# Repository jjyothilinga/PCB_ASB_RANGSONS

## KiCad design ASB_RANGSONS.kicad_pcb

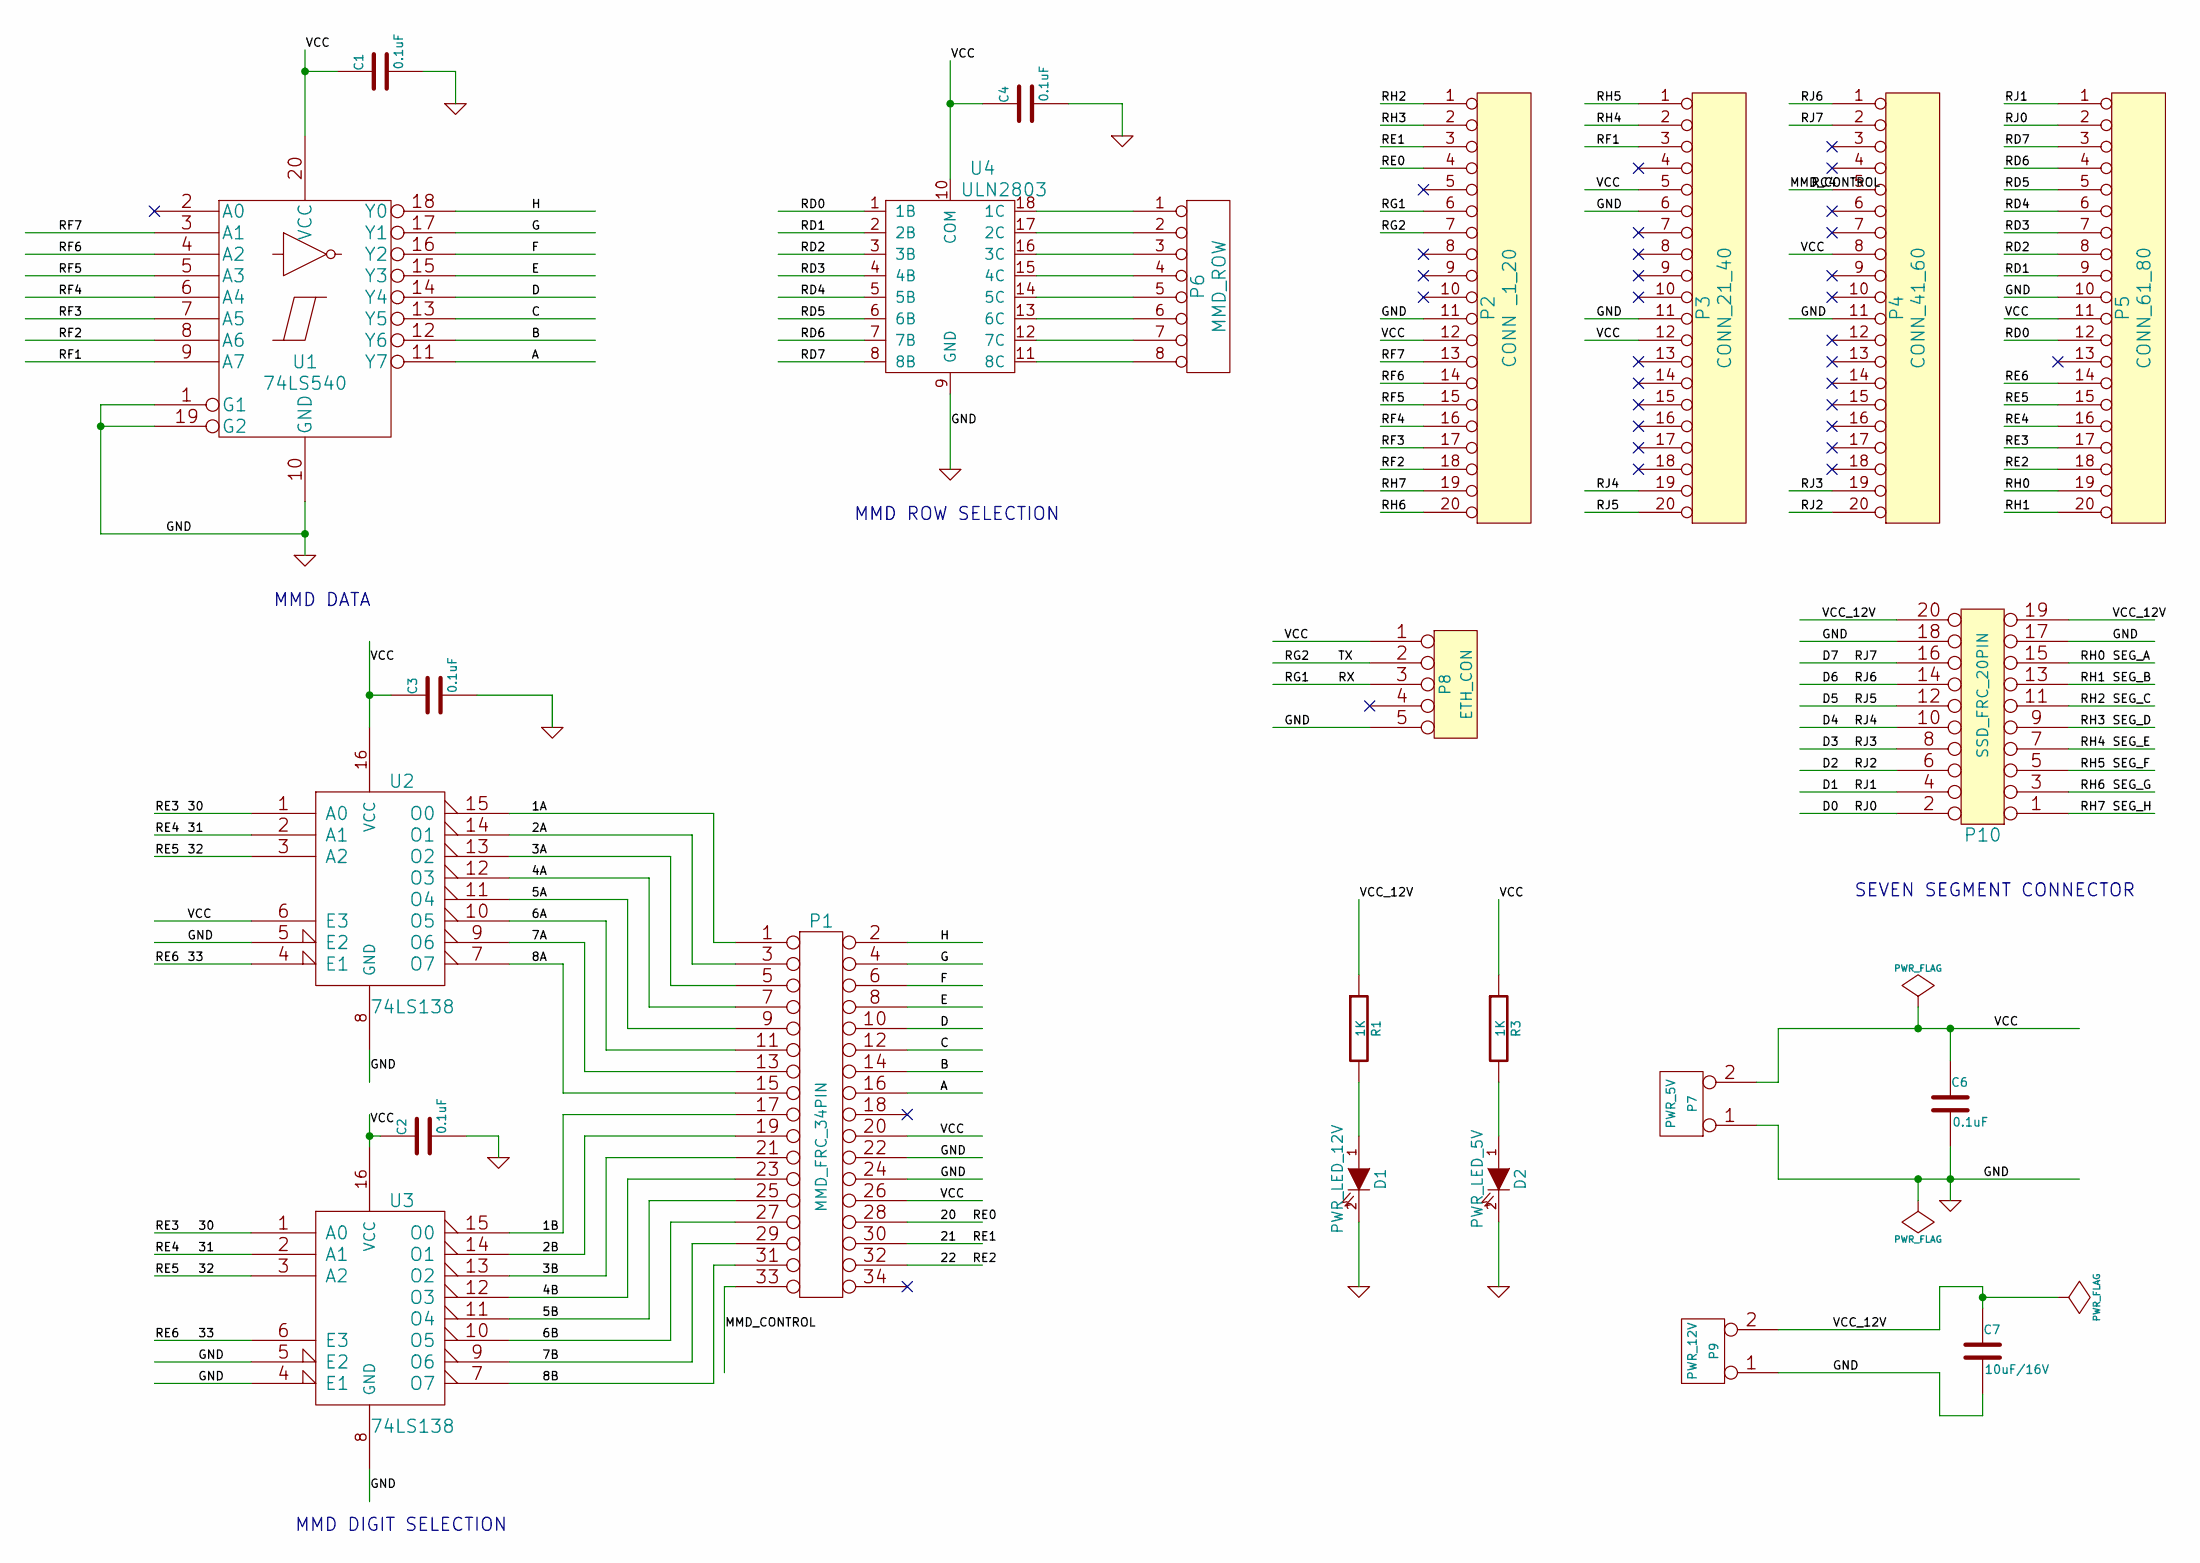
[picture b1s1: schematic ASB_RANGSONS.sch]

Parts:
C1, C2, C3, C4, C6: 0.1uF
C7: 10uF/16V
D1: PWR_LED_12V
D2: PWR_LED_5V
P1: MMD_FRC_34PIN
P2: CONN _1_20
P3: CONN_21_40
P4: CONN_41_60
P5: CONN_61_80
P6: MMD_ROW
P7: PWR_5V
P8: ETH_CON
P9: PWR_12V
P10: SSD_FRC_20PIN
R1, R3: 1K
U1: 74LS540
U2, U3: 74LS138
U4: ULN2803

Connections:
/1A: P1.1, U2.15 (O0)
/1B: P1.17, U3.15 (O0)
/2A: P1.3, U2.14 (O1)
/2B: P1.19, U3.14 (O1)
/3A: P1.5, U2.13 (O2)
/3B: P1.21, U3.13 (O2)
/4A: P1.7, U2.12 (O3)
/4B: P1.23, U3.12 (O3)
/5A: P1.9, U2.11 (O4)
/5B: P1.25, U3.11 (O4)
/6A: P1.11, U2.10 (O5)
/6B: P1.27, U3.10 (O5)
/7A: P1.13, U2.9 (O6)
/7B: P1.29, U3.9 (O6)
/8A: P1.15, U2.7 (O7)
/8B: P1.31, U3.7 (O7)
/20: P1.28, P2.4
/21: P1.30, P2.3
/22: P1.32, P5.18
/30: P5.17, U2.1 (A0), U3.1 (A0)
/31: P5.16, U2.2 (A1), U3.2 (A1)
/32: P5.15, U2.3 (A2), U3.3 (A2)
/33: P5.14, U2.4 (E1), U3.6 (E3)
/A: P1.16, U1.11 (Y7)
/B: P1.14, U1.12 (Y6)
/C: P1.12, U1.13 (Y5)
/D: P1.10, U1.14 (Y4)
/D0: P5.2, P10.2
/D1: P5.1, P10.4
/D2: P4.20, P10.6
/D3: P4.19, P10.8
/D4: P3.19, P10.10
/D5: P3.20, P10.12
/D6: P4.1, P10.14
/D7: P4.2, P10.16
/E: P1.8, U1.15 (Y3)
/F: P1.6, U1.16 (Y2)
/G: P1.4, U1.17 (Y1)
/H: P1.2, U1.18 (Y0)
/MMD_CONTROL: P1.33, P4.5
/RD0: P5.12, U4.1 (1B)
/RD1: P5.9, U4.2 (2B)
/RD2: P5.8, U4.3 (3B)
/RD3: P5.7, U4.4 (4B)
/RD4: P5.6, U4.5 (5B)
/RD5: P5.5, U4.6 (6B)
/RD6: P5.4, U4.7 (7B)
/RD7: P5.3, U4.8 (8B)
/RF1: P3.3, U1.9 (A7)
/RF2: P2.18, U1.8 (A6)
/RF3: P2.17, U1.7 (A5)
/RF4: P2.16, U1.6 (A4)
/RF5: P2.15, U1.5 (A3)
/RF6: P2.14, U1.4 (A2)
/RF7: P2.13, U1.3 (A1)
/RG1: P2.6, P8.3
/RG2: P2.7, P8.2
/RH0: P5.19, P10.15
/RH1: P5.20, P10.13
/RH2: P2.1, P10.11
/RH3: P2.2, P10.9
/RH4: P3.2, P10.7
/RH5: P3.1, P10.5
/RH6: P2.20, P10.3
/RH7: P2.19, P10.1
/VCC: C1.1, C2.1, C3.1, C4.1, C6.1, P1.20, P1.26, P2.12, P3.5, P3.12, P4.8, P5.11, P7.2 (PM), P8.1, R3.1, U1.20 (VCC), U2.6 (E3), U2.16 (VCC), U3.16 (VCC), U4.10 (COM)
/VCC_12V: C7.1, P9.2 (PM), P10.19, P10.20, R1.1
GND: C1.2, C2.2, C3.2, C4.2, C6.2, C7.2, D1.2 (K), D2.2 (K), P1.22, P1.24, P2.11, P3.6, P3.11, P4.11, P5.10, P7.1, P8.5, P9.1, P10.17, P10.18, U1.1 (G1), U1.10 (GND), U1.19 (G2), U2.5 (E2), U2.8 (GND), U3.4 (E1), U3.5 (E2), U3.8 (GND), U4.9 (GND)
unnamed: D1.1 (A), R1.2
unnamed: D2.1 (A), R3.2
unnamed: P6.1, U4.18 (1C)
unnamed: P6.2, U4.17 (2C)
unnamed: P6.3, U4.16 (3C)
unnamed: P6.4, U4.15 (4C)
unnamed: P6.5, U4.14 (5C)
unnamed: P6.6, U4.13 (6C)
unnamed: P6.7, U4.12 (7C)
unnamed: P6.8, U4.11 (8C)

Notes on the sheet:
MMD ROW SELECTION
MMD DATA
MMD DIGIT SELECTION
SEVEN SEGMENT CONNECTOR

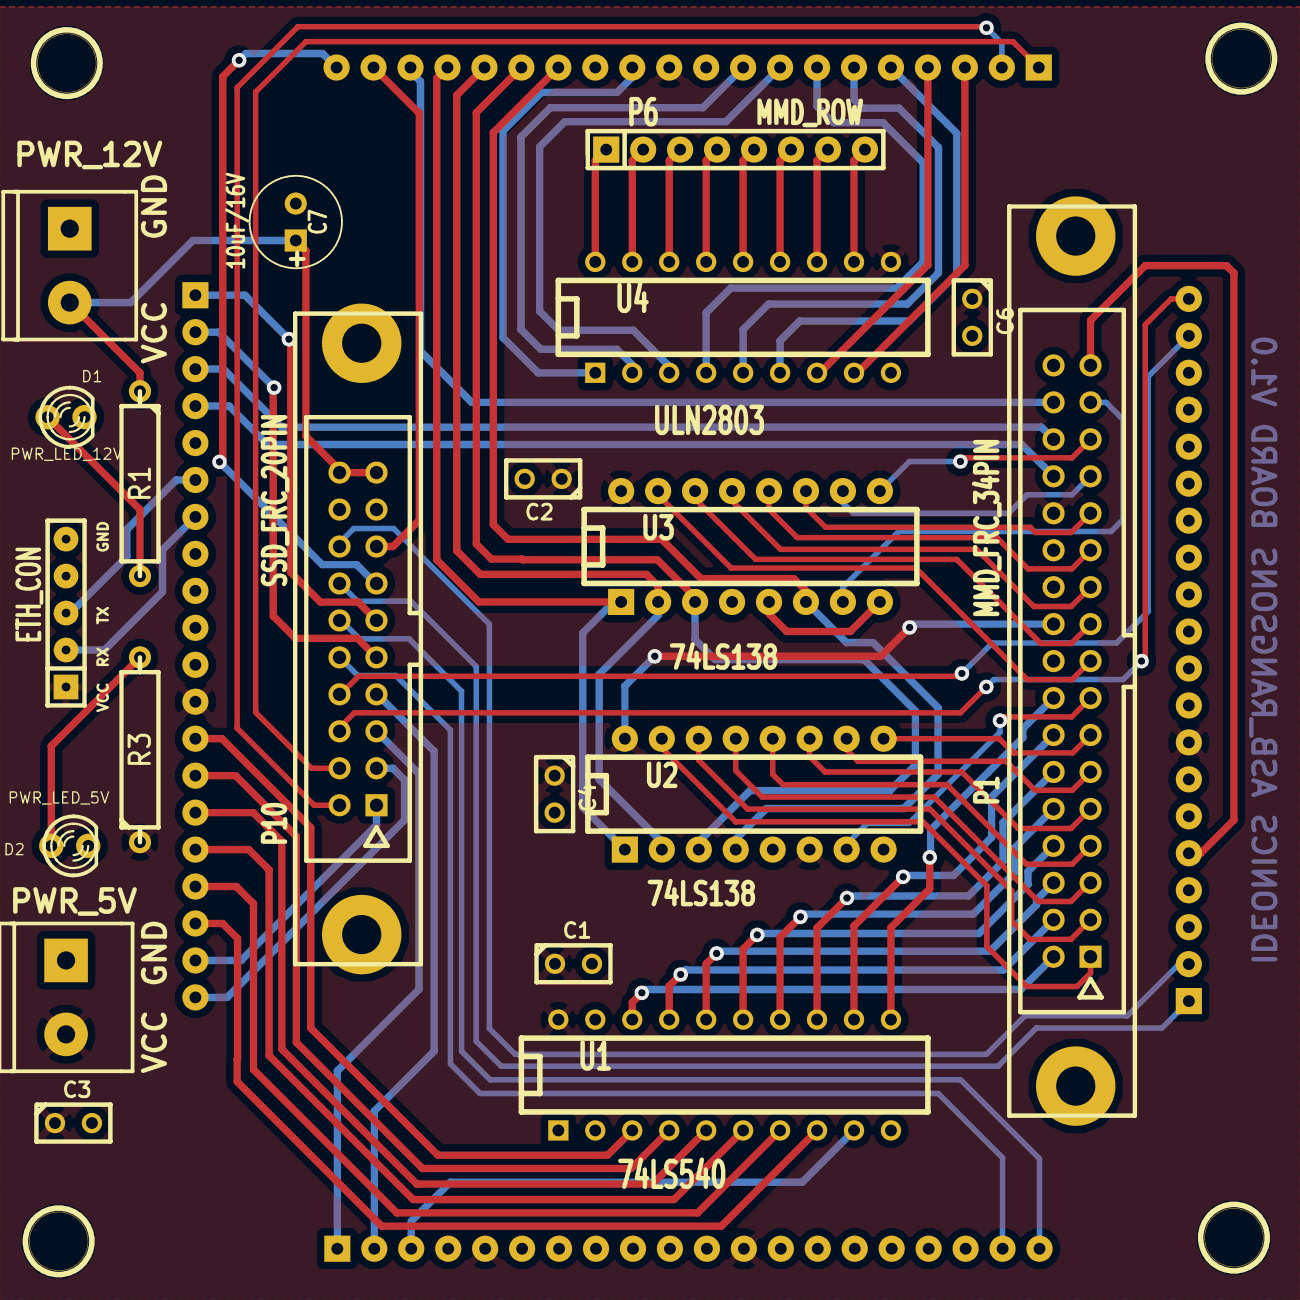
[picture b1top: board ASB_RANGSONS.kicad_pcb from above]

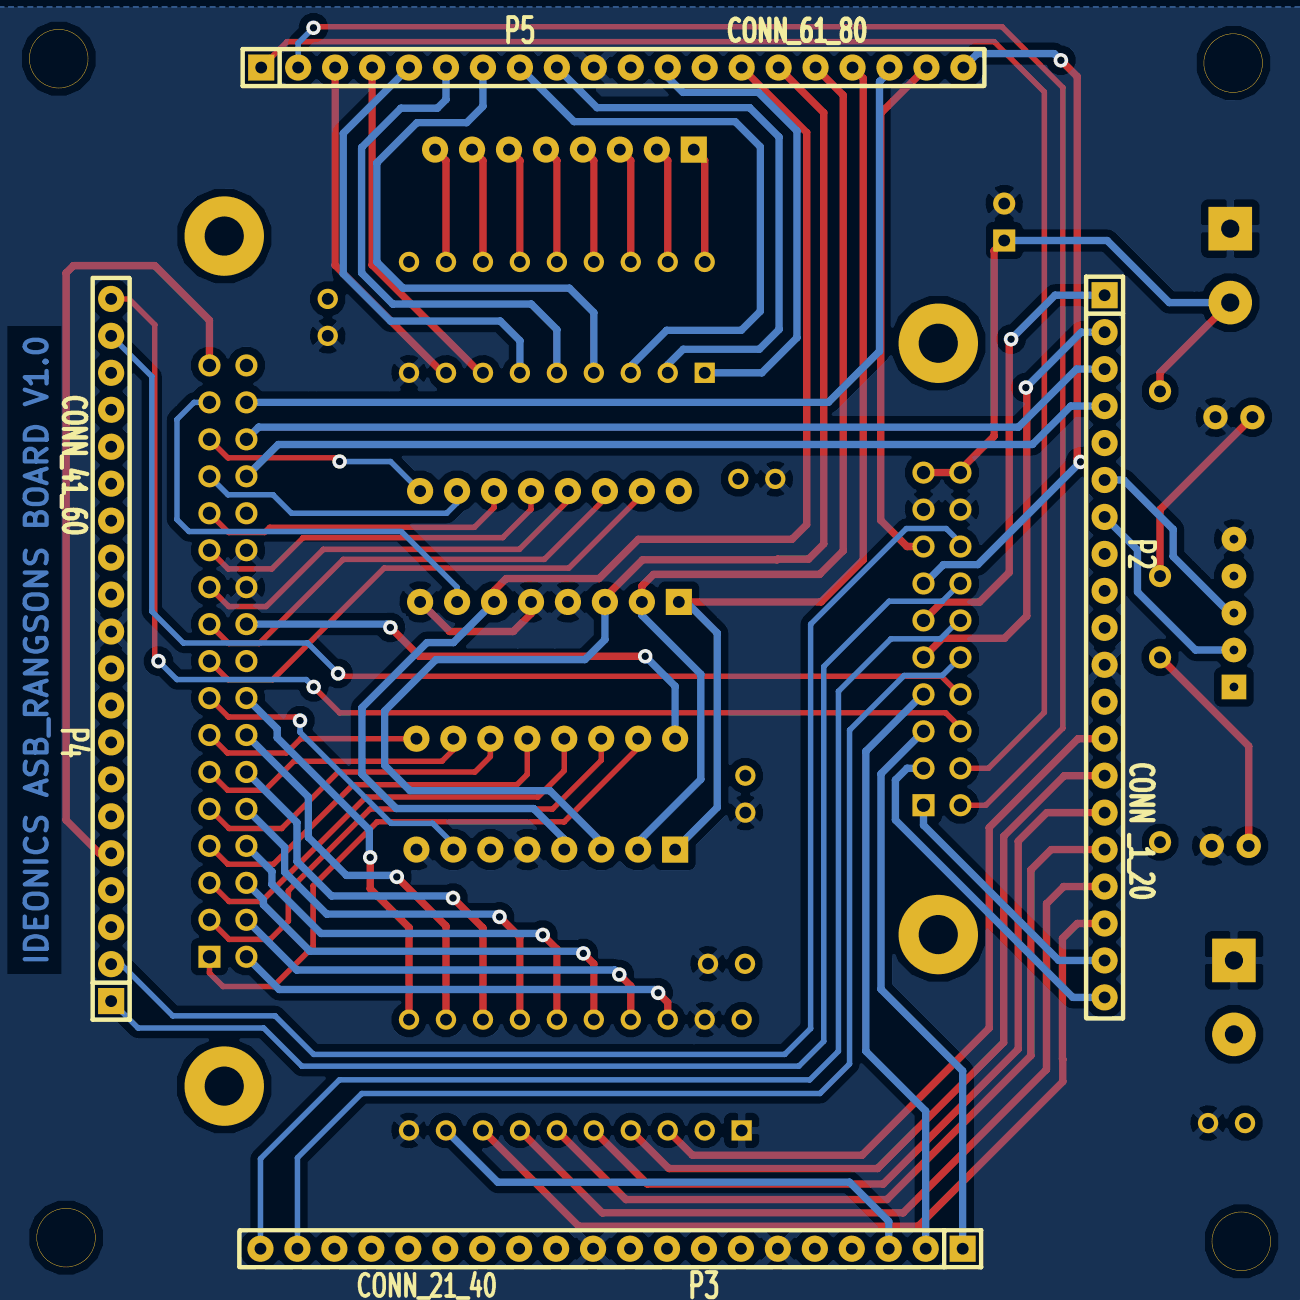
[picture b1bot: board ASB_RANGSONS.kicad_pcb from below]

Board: 2 copper layers, 28 parts (4 on the bottom side), 78 nets.

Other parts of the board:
1PIN, 1PIN#2, 1PIN#3, 1PIN#4: P***; 1pin

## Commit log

2015-03-18 :circus_tent: Added .gitattributes & .gitignore files
2015-03-18 Completed
2015-03-18 MMD_CONTROL_IS_MODIFIED
2015-03-19 Data lines modified as per led latch schematic
2015-08-07 Connector connection is modified
